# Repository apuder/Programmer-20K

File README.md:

# Programmer 20K

Web-based programmer for the Tang Primer 20K FPGA.

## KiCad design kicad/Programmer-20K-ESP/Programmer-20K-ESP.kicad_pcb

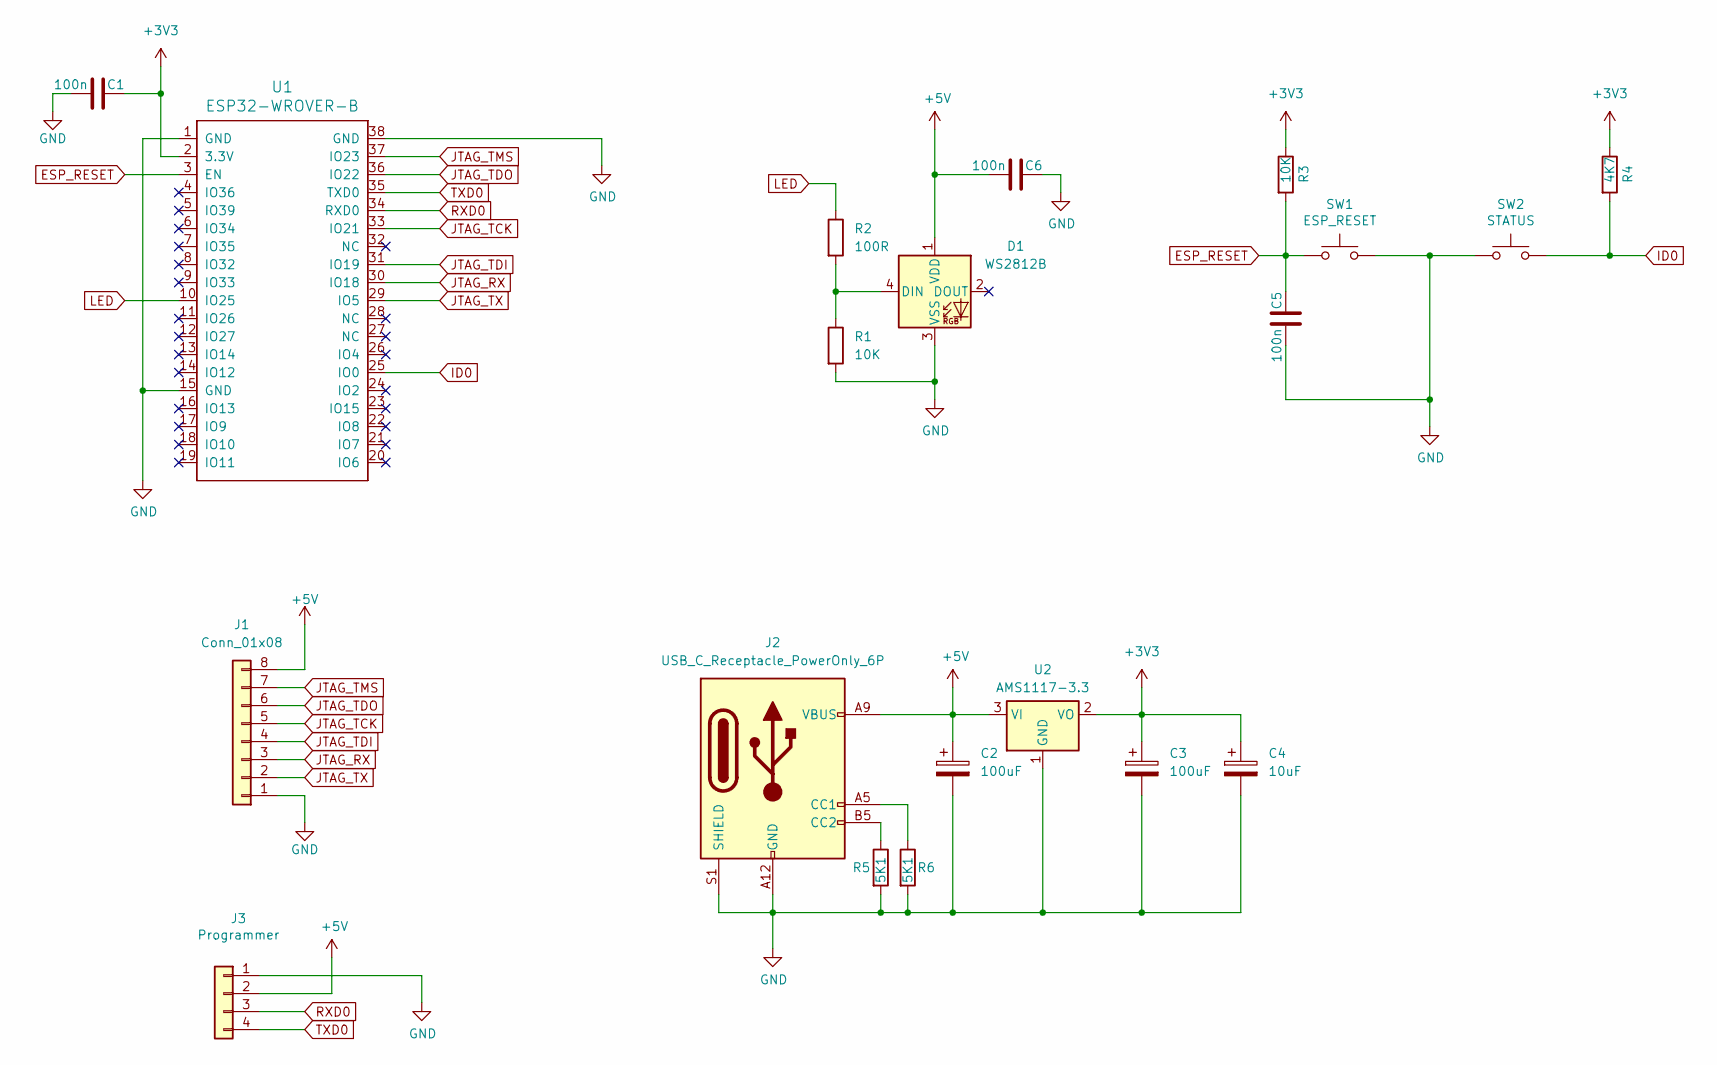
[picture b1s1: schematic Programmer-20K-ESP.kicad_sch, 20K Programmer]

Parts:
C1, C5, C6: 100n; C_0805_2012Metric_Pad1.18x1.45mm_HandSolder
C2, C3: 100uF; C_1206_3216Metric_Pad1.33x1.80mm_HandSolder; LCSC C1954161
C4: 10uF; C_1206_3216Metric_Pad1.33x1.80mm_HandSolder; LCSC C1952827
D1: WS2812B; LED_WS2812B_PLCC4_5.0x5.0mm_P3.2mm; LCSC C2761795
J1: Conn_01x08; PinHeader_1x08_P2.54mm_Vertical
J2: USB_C_Receptacle_PowerOnly_6P; USB_C_Receptacle_GCT_USB4125-xx-x_6P_TopMnt_Horizontal; LCSC C168701
J3: Programmer; PinHeader_1x04_P2.54mm_Vertical; LCSC C2691448
R1, R3: 10K; R_0805_2012Metric_Pad1.20x1.40mm_HandSolder
R2: 100R; R_0805_2012Metric_Pad1.20x1.40mm_HandSolder
R4: 4K7; R_0805_2012Metric_Pad1.20x1.40mm_HandSolder
R5, R6: 5K1; R_0805_2012Metric_Pad1.20x1.40mm_HandSolder
SW1: ESP_RESET; SW_Push_1P1T_NO_E-Switch_TL3301NxxxxxG; LCSC C255812
SW2: STATUS; SW_Push_1P1T_NO_E-Switch_TL3301NxxxxxG; LCSC C255812
U1: ESP32-WROVER-B; ESP32-WROVER; LCSC C967023
U2: AMS1117-3.3; SOT-223-3_TabPin2

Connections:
+3V3: C1.2, C3.1, C4.1, R3.1, R4.1, U1.2 (3.3V), U2.2 (VO)
+5V: C2.1, C6.1, D1.1 (VDD), J1.8, J2.A9 (VBUS), J2.B9 (VBUS), J3.2, U2.3 (VI)
ESP_RESET: C5.2, R3.2, SW1.1, U1.3 (EN)
GND: C1.1, C2.2, C3.2, C4.2, C5.1, C6.2, D1.3 (VSS), J1.1, J2.A12 (GND), J2.B12 (GND), J2.S1 (SHIELD), J3.1, R1.2, R5.2, R6.2, SW1.2, SW2.1, U1.1 (GND), U1.15 (GND), U1.38 (GND), U2.1 (GND)
ID0: R4.2, SW2.2, U1.25 (IO0)
JTAG_RX: J1.3, U1.30 (IO18)
JTAG_TCK: J1.5, U1.33 (IO21)
JTAG_TDI: J1.4, U1.31 (IO19)
JTAG_TDO: J1.6, U1.36 (IO22)
JTAG_TMS: J1.7, U1.37 (IO23)
JTAG_TX: J1.2, U1.29 (IO5)
LED: R2.1, U1.10 (IO25)
unnamed: D1.4 (DIN), R1.1, R2.2
unnamed: J2.A5 (CC1), R6.1
unnamed: J2.B5 (CC2), R5.1
RXD0: J3.3, U1.34 (RXD0)
TXD0: J3.4, U1.35 (TXD0)

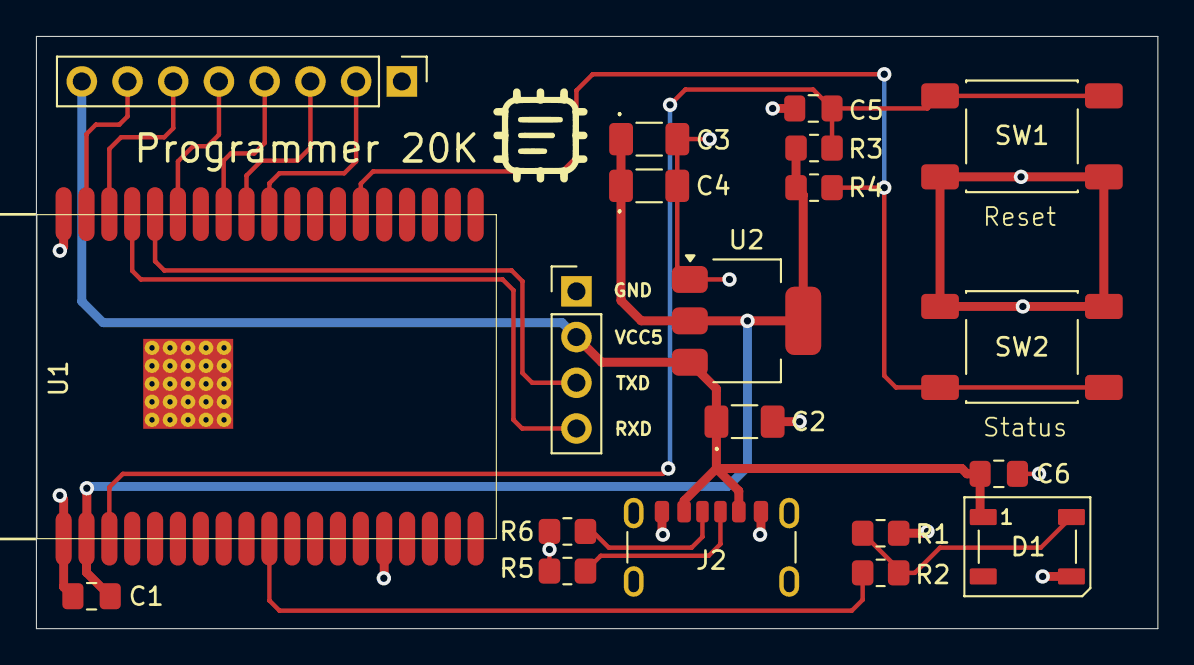
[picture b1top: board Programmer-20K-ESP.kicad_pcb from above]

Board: 2 copper layers, 62.3 x 32.9 mm, 20 parts (0 on the bottom side), 17 nets.

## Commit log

2025-12-24 Initial version
2025-12-24 Add serial monitor
2025-12-24 Add uploader for SRAM and Flash
2025-12-24 Skeleton README
2025-12-24 Remove 20K connected status
2025-12-24 Reorganize directory structure
2025-12-25 Only reboot FPGA when uploading to flash
2025-12-25 Add input to serial monitor
2025-12-26 Add favicon
2025-12-27 Compact PCB for the programmer
2026-01-29 Support for WS2812B RGB LED
2026-02-06 Minor UI tweaks
2026-02-06 Migrate to ESP-IDF 5
2026-05-31 Added configuration for MiniPC
2026-06-01 Fix the wrong RX/TX pins for Programmer20K board
2026-06-01 Support for terminal formatting via ESC sequence
2026-06-01 Upgrade to ESP-IDF 6
2026-06-01 More robust handling of stale websockets
2026-06-13 Support for LiteX firmware upload
